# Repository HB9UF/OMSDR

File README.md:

# OMSDR: An SMD soldering practice kit for hams

## Introduction

OMSDR is a simple HF SDR receiver frontend inspired by the [SoftRock Lite II](http://fivedash.com/index.php?main_page=product_info&products_id=5). It is designed as SMD soldering practice kit to demonstrate the power of SMD technology, meant as an entry point for amateur radio hobbyists who are afraid of SMD. To allow for an easy entrance, most components are fairly large -- much larger than what you usually use in SMD designs. Our position is that SMD soldering is not hard if you know the proper techniques, and that a kit such as this one makes it easy to acquire these techniques. Note that this is not a particular good radio, and if you are not in for the aforementioned SMD aspects, you are probably better off with a different kit. If one of the following is of interest to you, though, then this may be for you:

1. Easy to assemble SMD kit with large parts and large footprints designed for entry level SMD hand soldering.
2. This kit makes for a good learning experience if you are interested in the Tayloe mixer circuitry that is the basis for these types of SDR frontends. The relevant signals are easy to probe, allowing for a deeper understanding of the circuit.

The circuit stored in this repository is designed for the 40 meter amateur radio band, although it is relatively easy (and hopefully instructional) to alter the design for operation on another band. If you do so, we would very much like to hear from you.

## Schematic

## Key differences to Soft Rock Lite II
This is not an exact copy of the design by Tony Parks. Instead, we opted for the following key differences:

- You don't have to wind any magnetic components. We use SMD inductors in the frontend filter (which we redesigned somewhat) and we use an SMD transformer (CX2147NL) for the balun.

- The original design employs a common-collector Colpitts oscillator to generate the reference for the local oscillator. We replaced that with a Silabs si5351 clock generator for versatility.

- The reference from the aforementioned Colpitts oscillation is fed into a dual D-Flip-Flop to generate a quadrature clock in the original design, yielding two square waves at a quarter of the reference frequency with a phase difference of 90°. We generate the quadrature clock directly with the si5351 clock generator.

- We use a microcontroller to program the clock generator. We chose an Attiny24 for this but this can be easily swapped out for something else. The clock generator is programmed via I2C and this bus is accessible through a pin header. Thus you could choose not to populate the microcontroller and use, e.g., a Raspberry Pi instead. Using a programmable clock generator allows us to change the center frequency of the SDR within the band, thus covering the whole 40 meter band. The original design has a fixed oscillator at approx. 7.056 MHz, thus even if you use a sampling rate of 96 kHz, it only covers the lower half of the band.

- a 3.5 mm audio jack can be plugged directly into the OMSDR board to connect to the sound card.

- Our design is fully open source.

## Bill of Materials

A BOM csv file is available [here](https://raw.githubusercontent.com/HB9UF/OMSDR/master/doc/BOM_rev1.2.csv) -- note that there is an aggregated table at the bottom. The `BOM` column follows the `bomtool` format, which is a retired tool by Alexis Lockwood. Essentially, digikey order numbers are prefixed with `DIST DIGIKEY` and for passives, we specify parts requirements that used to be processed by `bomtool` to pick the cheapest available part from digikey. Let us know if you are looking for a BOM or have compiled one yourself -- we have to transition to a new BOM format and that would be a good motivation to do so. Please also note that we did not include the pin headers because we believe that most builders will have those in bulk, and also because it pays off to buy them in bulk. For assembly, we have an interactive BOM [here](https://htmlpreview.github.io/?https://github.com/HB9UF/OMSDR/master/doc/ibom_rev1.2.html).

## Firmware

Firmware is available in the `firmware` subdirectory. To compile, run `make` and then flash the microcontroller using your favorite method, for example:

```
avrdude -v -pt44 -cstk500v2 -Pusb -Uflash:w:40m.hex:i
```

On a Debian system or a distribution based on Debian, you will need the packages `make`, `gcc-avr`, `avr-libc`, `binutils-avr` and `avrdude`  for this to work.

On power-up, the firmware cycles through the LEDs and initialized the local oscillator at 7.020 MHz. With a sound card sampling at 48 kHz, you will have access to the spectrum between 6.996 MHz and 7.044 MHz, i.e., the low end of the 40 meter amateur radio band. In this mode, the leftmost LED will be on and the remaining LEDs will be off: `[x][ ][ ][ ]`. Pushing the bottom button moves the center frequency to 7.060 MHz, covering the spectrum from 7.036 MHz to 7.084 MHz. The corresponding LED indicator reads `[x][x][ ][ ]`. In this manner, you can tune through different portions of the band according to the following frequency plan (center frequency indicated in parentheses):

```
       [x][ ][ ][ ]       [x][x][ ][ ]        [ ][x][x][ ]        [ ][ ][x][x]       [ ][ ][ ][x]
6.996  --(7.020)--  7.044
7.000  --(7.020)--  7.040
                    7.036  --(7.060)--  7.084
                    7.040  --(7.060)--  7.080
                                        7.076  --(7.100)--  7.124
                                        7.080  --(7.100)--  7.120
                                                            7.116  --(7.140)-- 7.164
                                                            7.120  --(7.140)-- 7.160
                                                                               7.156  --(7.180)-- 7.204
                                                                               7.160  --(7.180)-- 7.200
```

## Dimensions

## Software and License
This board files were designed with KiCad 6. They are licensed under the CC-BY-SA license. More information on this license can be found [here](https://creativecommons.org/licenses/by-sa/4.0/). The software is licensed under the [GNU GENERAL PUBLIC LICENSE Version 3](https://www.gnu.org/licenses/gpl-3.0.en.html)

## References

The paper "Ultra Low Noise, High Performance, Zero IF Quadrature Product Detector and Preamplifier" by Dan Tayloe is a nice introduction to the principles of Tayloe quadrature product detectors. We are not sure where it was published originally, but it is available [here](http://www.norcalqrp.org/files/Tayloe_mixer_x3a.pdf). For a more intricate introduction, including software aspects, we refer to the article series "A Software-Defined Radio for the Masses" by Gerald Youngblood, published in the QEX journal in 2002 and 2003: [Part 1](https://www.arrl.org/files/file/Technology/tis/info/pdf/020708qex013.pdf), [Part 2](https://www.arrl.org/files/file/Technology/tis/info/pdf/020910qex010.pdf), [Part 3](https://www.arrl.org/files/file/Technology/tis/info/pdf/021112qex027.pdf), [Part 4](https://www.arrl.org/files/file/Technology/tis/info/pdf/030304qex020.pdf).

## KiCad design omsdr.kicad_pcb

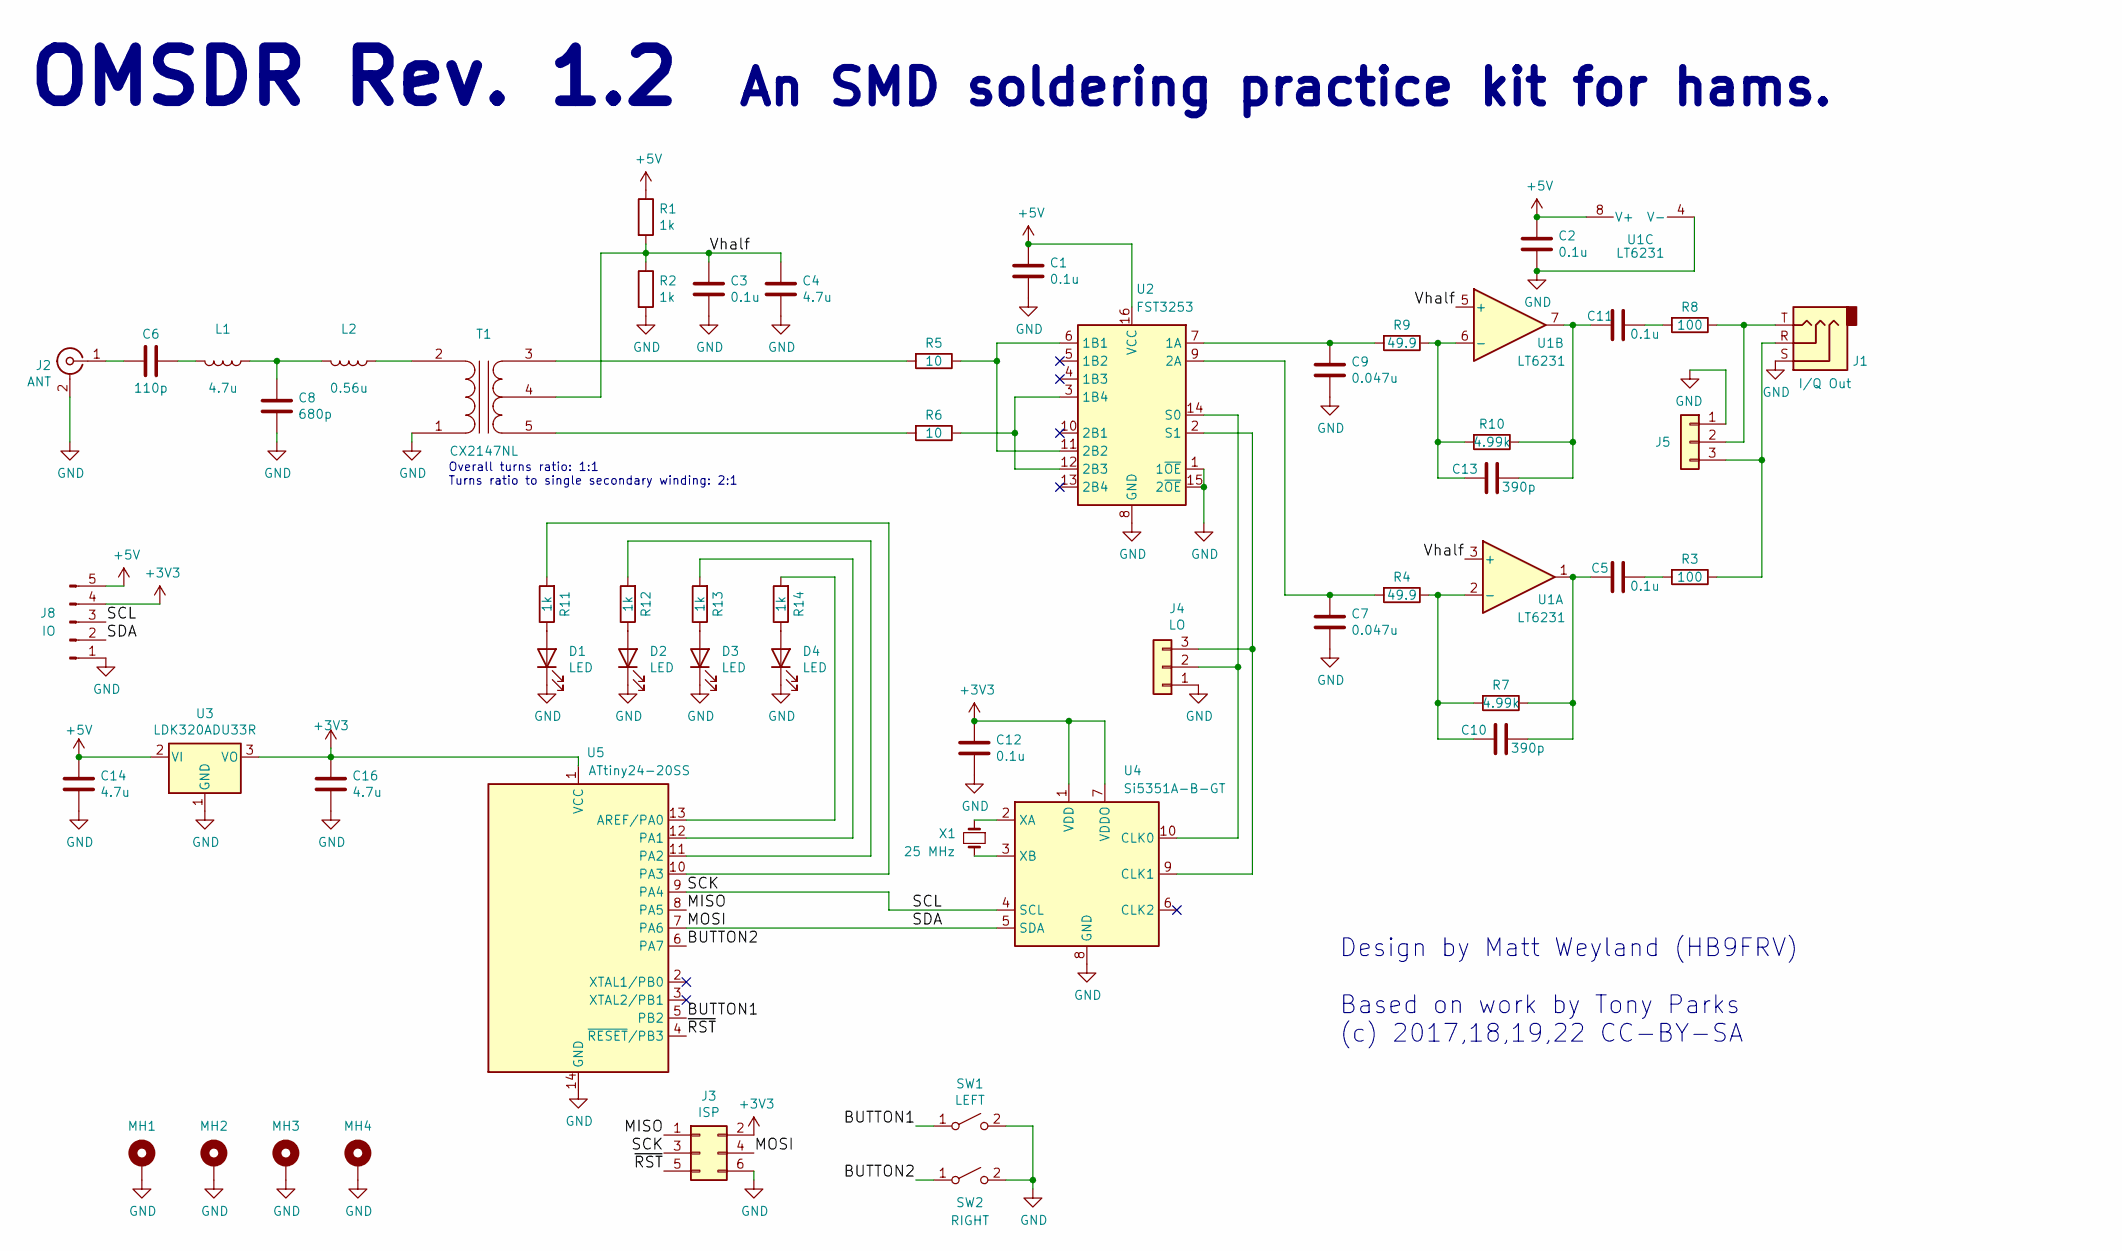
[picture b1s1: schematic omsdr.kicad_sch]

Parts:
C1, C2, C3, C5, C11, C12: 0.1u; C_1206_3216Metric_Pad1.33x1.80mm_HandSolder
C4, C14, C16: 4.7u; C_1206_3216Metric_Pad1.33x1.80mm_HandSolder
C6: 110p; C_1206_3216Metric_Pad1.33x1.80mm_HandSolder
C7, C9: 0.047u; C_1206_3216Metric_Pad1.33x1.80mm_HandSolder
C8: 680p; C_1206_3216Metric_Pad1.33x1.80mm_HandSolder
C10, C13: 390p; C_1206_3216Metric_Pad1.33x1.80mm_HandSolder
D1, D2, D3, D4: LED; LED_0805_2012Metric_Pad1.15x1.40mm_HandSolder
J1: I/Q Out; Jack_3.5mm_CUI_SJ-3523-SMT_Horizontal
J2: ANT; SMA_Samtec_SMA-J-P-X-ST-EM1_EdgeMount
J3: ISP; PinHeader_2x03_P2.54mm_Vertical
J4: LO; PinHeader_1x03_P2.54mm_Vertical
J5: I/Q Out; PinHeader_1x03_P2.54mm_Vertical
J8: IO; PinHeader_1x05_P2.54mm_Horizontal
L1: 4.7u; L_1206_3216Metric_Pad1.42x1.75mm_HandSolder
L2: 0.56u; L_0805_2012Metric_Pad1.15x1.40mm_HandSolder
MH1, MH2, MH3, MH4: MountingHole_3.2mm_M3_Pad_Via
R1, R2, R11, R12, R13, R14: 1k; R_1206_3216Metric_Pad1.30x1.75mm_HandSolder
R3, R8: 100; R_1206_3216Metric_Pad1.30x1.75mm_HandSolder
R4, R9: 49.9; R_1206_3216Metric_Pad1.30x1.75mm_HandSolder
R5, R6: 10; R_1206_3216Metric_Pad1.30x1.75mm_HandSolder
R7, R10: 4.99k; R_1206_3216Metric_Pad1.30x1.75mm_HandSolder
SW1: LEFT; SW_SPST_TL3342
SW2: RIGHT; SW_SPST_TL3342
T1: CX2147NL; CX2074
U1: LT6231; SO-8_3.9x4.9mm_P1.27mm
U2: FST3253; SOIC-16_3.9x9.9mm_P1.27mm
U3: LDK320ADU33R; SOT-89-3_Handsoldering
U4: Si5351A-B-GT; MSOP-10_3x3mm_P0.5mm
U5: ATtiny24-20SS; SOIC-14_3.9x8.7mm_P1.27mm
X1: 25 MHz; Crystal_SMD_HC49-SD

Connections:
+3V3: C12.1, C16.1, J3.2, J8.4, U3.3 (VO), U4.1 (VDD), U4.7 (VDDO), U5.1 (VCC)
+5V: C1.1, C2.1, C14.1, J8.5, R1.1, U1.8 (V+), U2.16 (VCC), U3.2 (VI)
/BUTTON1: SW1.1 (A), U5.5 (PB2)
/BUTTON2: SW2.1 (A), U5.6 (PA7)
/MISO: J3.1, U5.8 (PA5)
/MOSI: J3.4, J8.2, U4.5 (SDA), U5.7 (PA6)
/SCK: J3.3, J8.3, U4.4 (SCL), U5.9 (PA4)
/Vhalf: C3.1, C4.1, R1.2, R2.1, T1.4 (SC), U1.3 (+), U1.5 (+)
/~RST: J3.5, U5.4 (~RESET/PB3)
GND: C1.2, C2.2, C3.2, C4.2, C7.2, C8.2, C9.2, C12.2, C14.2, C16.2, D1.1 (K), D2.1 (K), D3.1 (K), D4.1 (K), J1.S, J2.2 (Ext), J3.6, J4.1, J5.1, J8.1, MH1.1, MH2.1, MH3.1, MH4.1, R2.2, SW1.2 (B), SW2.2 (B), T1.1 (AA), U1.4 (V-), U2.1 (1~OE), U2.8 (GND), U2.15 (2~OE), U3.1 (GND), U4.8 (GND), U5.14 (GND)
unnamed: C5.2, R3.2
unnamed: C6.1, L1.2
unnamed: C6.2, J2.1 (In)
unnamed: C7.1, R4.2, U2.9 (2A)
unnamed: C8.1, L1.1, L2.2
unnamed: C9.1, R9.2, U2.7 (1A)
unnamed: C10.1, R4.1, R7.2, U1.2 (-)
unnamed: C5.1, C10.2, R7.1, U1.1
unnamed: C11.1, C13.2, R10.1, U1.7
unnamed: C11.2, R8.2
unnamed: C13.1, R9.1, R10.2, U1.6 (-)
unnamed: D1.2 (A), R11.1
unnamed: D2.2 (A), R12.1
unnamed: D3.2 (A), R13.1
unnamed: D4.2 (A), R14.1
unnamed: J1.R, J5.3, R3.1
unnamed: J1.T, J5.2, R8.1
unnamed: J4.2, U2.14 (S0), U4.10 (CLK0)
unnamed: J4.3, U2.2 (S1), U4.9 (CLK1)
unnamed: L2.1, T1.2 (AB)
unnamed: R5.1, U2.6 (1B1), U2.11 (2B2)
unnamed: R5.2, T1.3 (SA)
unnamed: R6.1, U2.3 (1B4), U2.12 (2B3)
unnamed: R6.2, T1.5 (SB)
unnamed: R11.2, U5.10 (PA3)
unnamed: R12.2, U5.11 (PA2)
unnamed: R13.2, U5.12 (PA1)
unnamed: R14.2, U5.13 (AREF/PA0)
unnamed: U4.2 (XA), X1.1
unnamed: U4.3 (XB), X1.2

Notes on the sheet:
An SMD soldering practice kit for hams.
Overall turns ratio: 1:1 Turns ratio to single secondary winding: 2:1
Design by Matt Weyland (HB9FRV) Based on work by Tony Parks (c) 2017,18,19,22 CC-BY-SA
OMSDR Rev. 1.2

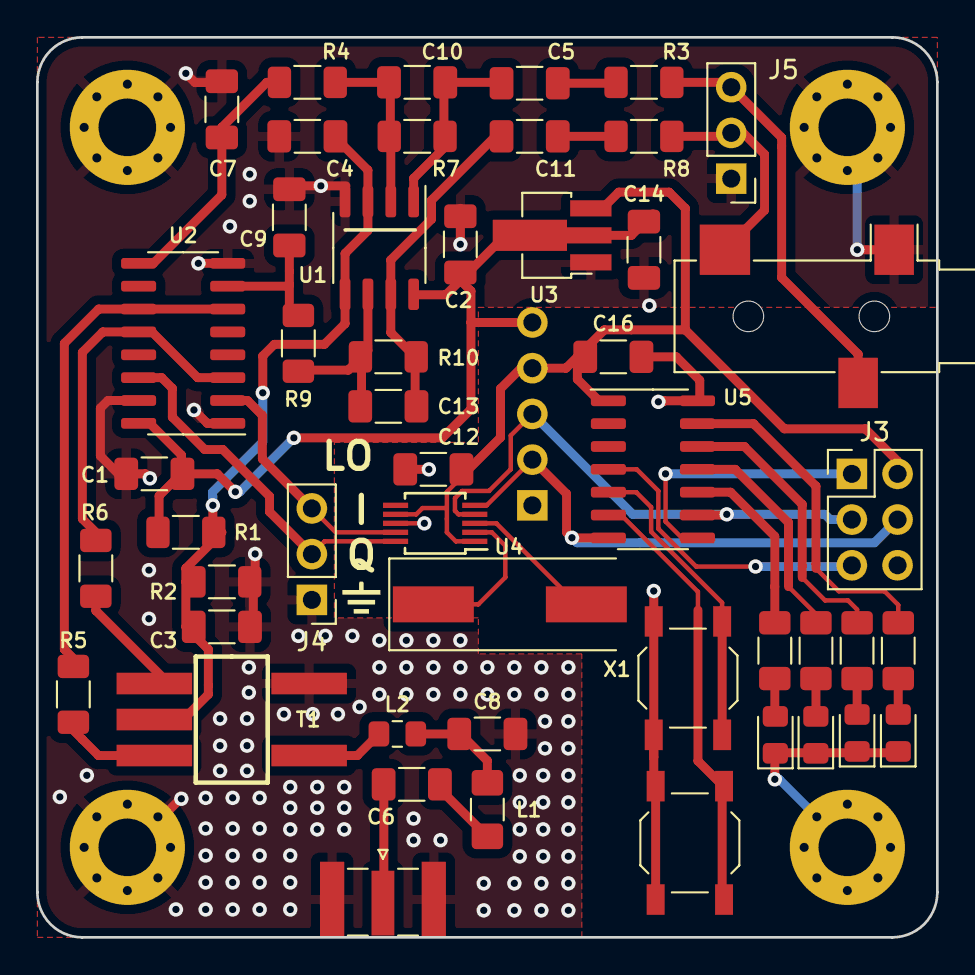
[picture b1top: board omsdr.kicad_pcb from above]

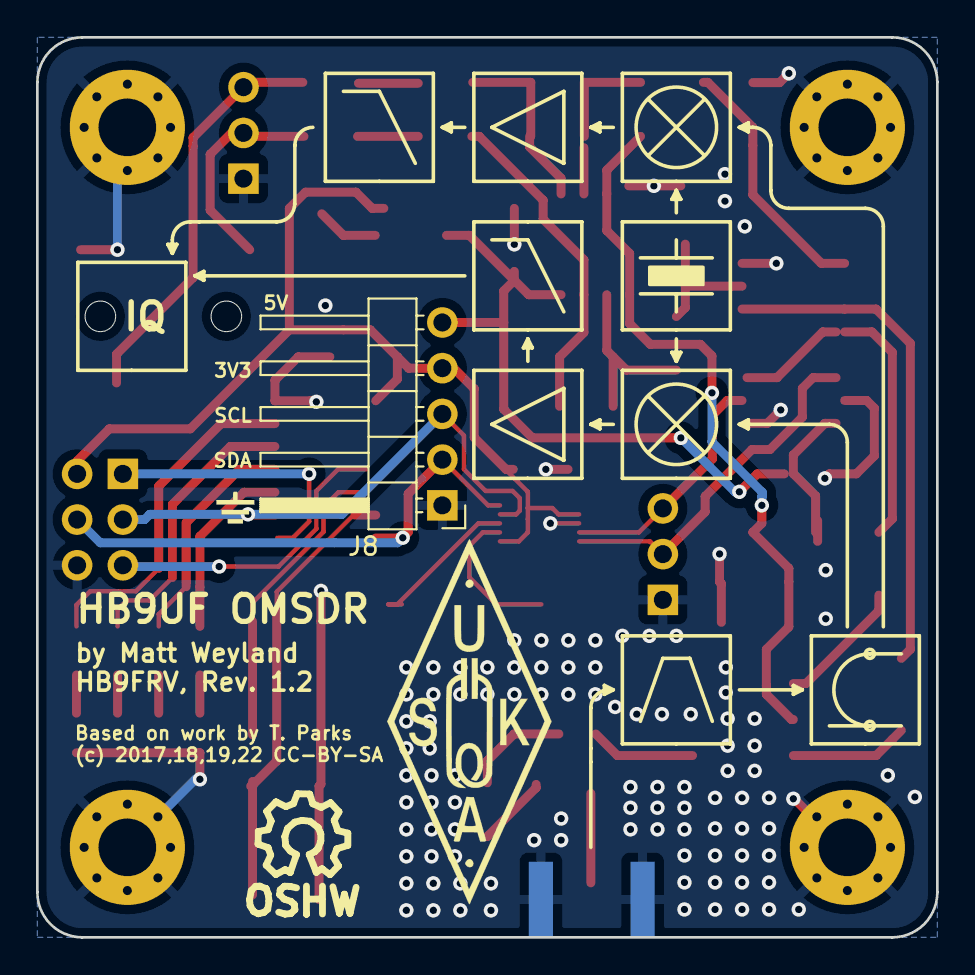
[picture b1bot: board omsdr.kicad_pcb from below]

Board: 2 copper layers, 50.0 x 50.0 mm, 57 parts (3 on the bottom side), 40 nets.

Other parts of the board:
SYM: Symbol_OSHW-Logo_SilkScreen_07Jul2012; Symbol_OSHW-Logo_SilkScreen
VAL: GND
VAL#2: GND

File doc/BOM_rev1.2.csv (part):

"Individual Components:"

"Item","Qty","Reference(s)","Value","LibPart","Footprint","Datasheet","BOM"
"","","C1","0.1u","Device:C","Capacitor_SMD:C_1206_3216Metric_Pad1.33x1.80mm_HandSolder","~","CAP MLCC 0.1u  ±10% ≥X7R [1206]"
"","","C2","0.1u","Device:C","Capacitor_SMD:C_1206_3216Metric_Pad1.33x1.80mm_HandSolder","~","CAP MLCC 0.1u  ±10% ≥X7R [1206]"
"","","C3","0.1u","Device:C","Capacitor_SMD:C_1206_3216Metric_Pad1.33x1.80mm_HandSolder","~","CAP MLCC 0.1u  ±10% ≥X7R [1206]"
"","","C4","4.7u","Device:C","Capacitor_SMD:C_1206_3216Metric_Pad1.33x1.80mm_HandSolder","~","CAP MLCC 4.7u ±20% 10V [1206]"
"","","C5","0.1u","Device:C","Capacitor_SMD:C_1206_3216Metric_Pad1.33x1.80mm_HandSolder","~","CAP MLCC 0.1u  ±10% ≥X7R [1206]"
"","","C6","110p","Device:C","Capacitor_SMD:C_1206_3216Metric_Pad1.33x1.80mm_HandSolder","~","CAP MLCC 110p ±5% NP0 [1206]"
"","","C7","0.047u","Device:C","Capacitor_SMD:C_1206_3216Metric_Pad1.33x1.80mm_HandSolder","~","CAP MLCC 0.047u ±10% ≥X5R [1206]"
"","","C8","680p","Device:C","Capacitor_SMD:C_1206_3216Metric_Pad1.33x1.80mm_HandSolder","~","CAP MLCC 680p  ±5% NP0 [1206]"
"","","C9","0.047u","Device:C","Capacitor_SMD:C_1206_3216Metric_Pad1.33x1.80mm_HandSolder","~","CAP MLCC 0.047u ±10% ≥X5R [1206]"
"","","C10","390p","Device:C","Capacitor_SMD:C_1206_3216Metric_Pad1.33x1.80mm_HandSolder","~","CAP MLCC 390p  ±5% NP0 [1206]"
"","","C11","0.1u","Device:C","Capacitor_SMD:C_1206_3216Metric_Pad1.33x1.80mm_HandSolder","~","CAP MLCC 0.1u  ±10% ≥X7R [1206]"
"","","C12","0.1u","Device:C","Capacitor_SMD:C_1206_3216Metric_Pad1.33x1.80mm_HandSolder","~","CAP MLCC 0.1u  ±10% ≥X7R [1206]"
"","","C13","390p","Device:C","Capacitor_SMD:C_1206_3216Metric_Pad1.33x1.80mm_HandSolder","~","CAP MLCC 390p  ±5% NP0 [1206]"
"","","C14","4.7u","Device:C","Capacitor_SMD:C_1206_3216Metric_Pad1.33x1.80mm_HandSolder","~","CAP MLCC 4.7u ±20% 10V [1206]"
"","","C16","4.7u","Device:C","Capacitor_SMD:C_1206_3216Metric_Pad1.33x1.80mm_HandSolder","~","CAP MLCC 4.7u ±20% 10V [1206]"
"","","D1","LED","Device:LED","LED_SMD:LED_0805_2012Metric_Pad1.15x1.40mm_HandSolder","~","DIST DIGIKEY 732-4984-1-ND"
"","","D2","LED","Device:LED","LED_SMD:LED_0805_2012Metric_Pad1.15x1.40mm_HandSolder","~","DIST DIGIKEY 732-4984-1-ND"
"","","D3","LED","Device:LED","LED_SMD:LED_0805_2012Metric_Pad1.15x1.40mm_HandSolder","~","DIST DIGIKEY 732-4984-1-ND"
"","","D4","LED","Device:LED","LED_SMD:LED_0805_2012Metric_Pad1.15x1.40mm_HandSolder","~","DIST DIGIKEY 732-4984-1-ND"
"","","J1","I/Q Out","Connector:AudioJack3","Connector_Audio:Jack_3.5mm_CUI_SJ-3523-SMT_Horizontal","~","DIST DIGIKEY CP-3523SJCT-ND"
"","","J2","ANT","Connector:Conn_Coaxial","Connector_Coaxial:SMA_Samtec_SMA-J-P-X-ST-EM1_EdgeMount"," ~","DIST DIGIKEY CON-SMA-EDGE-S-ND "
"","","J3","ISP","Connector_Generic:Conn_02x03_Odd_Even","Connector_PinHeader_2.54mm:PinHeader_2x03_P2.54mm_Vertical","~","DIST DIGIKEY 609-2846-ND"
"","","J4","LO","Connector_Generic:Conn_01x03","Connector_PinHeader_2.54mm:PinHeader_1x03_P2.54mm_Vertical","~",""
"","","J5","I/Q Out","Connector_Generic:Conn_01x03","Connector_PinHeader_2.54mm:PinHeader_1x03_P2.54mm_Vertical","~",""
"","","J8","IO","Connector:Conn_01x05_Male","Connector_PinHeader_2.54mm:PinHeader_1x05_P2.54mm_Horizontal","~",""
"","","L1","4.7u","Device:L","Inductor_SMD:L_1206_3216Metric_Pad1.42x1.75mm_HandSolder","~","DIST DIGIKEY  587-2034-1-ND"
"","","L2","0.56u","Device:L","Inductor_SMD:L_0805_2012Metric_Pad1.15x1.40mm_HandSolder","~","DIST DIGIKEY  LBM2016TR56J"
"","","MH1","","Mechanical:MountingHole_Pad","MountingHole:MountingHole_3.2mm_M3_Pad_Via","~",""
"","","MH2","","Mechanical:MountingHole_Pad","MountingHole:MountingHole_3.2mm_M3_Pad_Via","~",""
"","","MH3","","Mechanical:MountingHole_Pad","MountingHole:MountingHole_3.2mm_M3_Pad_Via","~",""
"","","MH4","","Mechanical:MountingHole_Pad","MountingHole:MountingHole_3.2mm_M3_Pad_Via","~",""
"","","R1","1k","Device:R","Resistor_SMD:R_1206_3216Metric_Pad1.30x1.75mm_HandSolder","~","RES SMD 1k 1% [1206]"
"","","R2","1k","Device:R","Resistor_SMD:R_1206_3216Metric_Pad1.30x1.75mm_HandSolder","~","RES SMD 1k 1% [1206]"
"","","R3","100","Device:R","Resistor_SMD:R_1206_3216Metric_Pad1.30x1.75mm_HandSolder","~","RES SMD 100 1% [1206]"
"","","R4","49.9","Device:R","Resistor_SMD:R_1206_3216Metric_Pad1.30x1.75mm_HandSolder","~","RES SMD 49.9 1% [1206]"
"","","R5","10","Device:R","Resistor_SMD:R_1206_3216Metric_Pad1.30x1.75mm_HandSolder","~","RES SMD 10 1% [1206]"
"","","R6","10","Device:R","Resistor_SMD:R_1206_3216Metric_Pad1.30x1.75mm_HandSolder","~","RES SMD 10 1% [1206]"
"","","R7","4.99k","Device:R","Resistor_SMD:R_1206_3216Metric_Pad1.30x1.75mm_HandSolder","~","RES SMD 4.99k 1% [1206]"
"","","R8","100","Device:R","Resistor_SMD:R_1206_3216Metric_Pad1.30x1.75mm_HandSolder","~","RES SMD 100 1% [1206]"
"","","R9","49.9","Device:R","Resistor_SMD:R_1206_3216Metric_Pad1.30x1.75mm_HandSolder","~","RES SMD 49.9 1% [1206]"
"","","R10","4.99k","Device:R","Resistor_SMD:R_1206_3216Metric_Pad1.30x1.75mm_HandSolder","~","RES SMD 4.99k 1% [1206]"
"","","R11","1k","Device:R","Resistor_SMD:R_1206_3216Metric_Pad1.30x1.75mm_HandSolder","~","RES SMD 1k 1% [0805]"
"","","R12","1k","Device:R","Resistor_SMD:R_1206_3216Metric_Pad1.30x1.75mm_HandSolder","~","RES SMD 1k 1% [0805]"
"","","R13","1k","Device:R","Resistor_SMD:R_1206_3216Metric_Pad1.30x1.75mm_HandSolder","~","RES SMD 1k 1% [0805]"
"","","R14","1k","Device:R","Resistor_SMD:R_1206_3216Metric_Pad1.30x1.75mm_HandSolder","~","RES SMD 1k 1% [0805]"
"","","SW1","LEFT","Switch:SW_SPST","Button_Switch_SMD:SW_SPST_TL3342","~","DIST DIGIKEY EG2531CT-ND"
"","","SW2","RIGHT","Switch:SW_SPST","Button_Switch_SMD:SW_SPST_TL3342","~","DIST DIGIKEY EG2531CT-ND"
"","","T1","CX2147NL","Device:Transformer_1P_SS","local:CX2074","~","DIST DIGIKEY 553-1501-ND"
"","","U1","LT6231","Amplifier_Operational:LT6234","Package_SO:SO-8_3.9x4.9mm_P1.27mm","https://www.analog.com/media/en/technical-documentation/data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","DIST DIGIKEY  LT6231CS8#PBF-ND"
"","","U2","FST3253","Analog_Switch:SN74CBT3253","Package_SO:SOIC-16_3.9x9.9mm_P1.27mm","https://www.fairchildsemi.com/datasheets/FS/FST3253.pdf","DIST DIGIKEY 296-19206-1-ND"
"","","U3","LDK320ADU33R","Regulator_Linear:MCP1703A-3302_SOT89","Package_TO_SOT_SMD:SOT-89-3_Handsoldering","http://ww1.microchip.com/downloads/en/DeviceDoc/20005122B.pdf","DIST DIGIKEY 497-17585-1-ND"
"","","U4","Si5351A-B-GT","Oscillator:Si5351A-B-GT","Package_SO:MSOP-10_3x3mm_P0.5mm","https://www.silabs.com/documents/public/data-sheets/Si5351-B.pdf","DIST DIGIKEY 336-3908-1-ND"
"","","U5","ATtiny24-20SS","MCU_Microchip_ATtiny:ATtiny24-20SS","Package_SO:SOIC-14_3.9x8.7mm_P1.27mm","http://ww1.microchip.com/downloads/en/DeviceDoc/doc8006.pdf","DIST DIGIKEY  ATTINY24A-SSU-ND"
"","","X1","25 MHz","Device:Crystal_Small","Crystal:Crystal_SMD_HC49-SD","~","DIST DIGIKEY  535-10235-1-ND"



"Collated Components:"

"Item","Qty","Reference(s)","Value","LibPart","Footprint","Datasheet","BOM"
"1","6","C1, C2, C3, C5, C11, C12","0.1u","Device:C","Capacitor_SMD:C_1206_3216Metric_Pad1.33x1.80mm_HandSolder","~","CAP MLCC 0.1u  ±10% ≥X7R [1206]"
"2","3","C4, C14, C16","4.7u","Device:C","Capacitor_SMD:C_1206_3216Metric_Pad1.33x1.80mm_HandSolder","~","CAP MLCC 4.7u ±20% 10V [1206]"
"3","1","C6","110p","Device:C","Capacitor_SMD:C_1206_3216Metric_Pad1.33x1.80mm_HandSolder","~","CAP MLCC 110p ±5% NP0 [1206]"
"4","2","C7, C9","0.047u","Device:C","Capacitor_SMD:C_1206_3216Metric_Pad1.33x1.80mm_HandSolder","~","CAP MLCC 0.047u ±10% ≥X5R [1206]"
"5","1","C8","680p","Device:C","Capacitor_SMD:C_1206_3216Metric_Pad1.33x1.80mm_HandSolder","~","CAP MLCC 680p  ±5% NP0 [1206]"
"6","2","C10, C13","390p","Device:C","Capacitor_SMD:C_1206_3216Metric_Pad1.33x1.80mm_HandSolder","~","CAP MLCC 390p  ±5% NP0 [1206]"
"7","4","D1, D2, D3, D4","LED","Device:LED","LED_SMD:LED_0805_2012Metric_Pad1.15x1.40mm_HandSolder","~","DIST DIGIKEY 732-4984-1-ND"
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
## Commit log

2018-01-10 Initial commit on the road to v1.1
2018-01-10 Initial commit of local 3d models
2018-01-10 Fix paths to local 3d models
2018-01-10 Adding utility to generate 2d renders using gerbv
2018-01-17 Replace 3.3 V regul L78L33ABUTR with LDK320ADU33R
    Almost same price, lower noise, better PSSR and slightly better
    pinout. Same SOT-89 package. Chances in schematic and PCB.
2018-01-18 Replacing crystal 3d model with step file that renders properly.
2018-01-21 Added missing silk screen line
2018-01-21 Don't create gerber report
2018-02-06 register_map_5mc_10mc.txt file for 5 MHz / 10 MHz test pattern with bus pirate
2018-02-06 Adding LICENSE file for code that will follow.
2018-02-06 Adding simple blink program to test microcontroller
2018-02-06 Moving blink.c and Makefile out of subdirectory
2018-02-13 Changed sample cap loading resistor frorm 10 Ohms to 49.9 Ohms
2018-02-13 Component values for opamp feedback network
2018-02-13 Multiplexer chip EOL, replaced with substitute order number
2019-03-14 Updating PCB from schematic (no formal changes)
2019-03-15 Adding more component values and BOM digikey order numbers
2019-03-15 Changes due to new kicad version (library upgrades etc.)
2019-03-15 Change Makefile.blink from attiny44 to attiny24
2019-03-15 Bumping kicad-schlib to latest version of upstream
2019-03-15 Use FST3253 from kicad-schlib instead of cached
2019-03-17 Replacing SMA connector since the one used was phased out from kicad
    No BOM as we are better off ordering this from China
2019-03-17 Changed my mind: Swapped SMA edge connector for smaller version
2019-03-17 Fixed silk screen of filter icon on back side of PCB
2019-03-17 Adding line to silk screen to indicate tiled edge of LT6231 package
2019-03-17 Reworked input bandpass filter
2019-03-17 Updated copyright dates
2019-03-17 Replaced footprints with versions from new kicad footprint library
2019-03-17 Adding pin header for IQ audio tap
2019-03-17 Replaced connector footprints with versions from new kicad footprint library
2019-03-17 Adding missing BOM fields
2019-03-17 Bumping version to 1.2 on schematic and PCB
2019-05-20 New copyright owners for 1.2 version of the project.
2019-05-20 Now official HB9UF project, add logo and rework silk.
2022-01-25 Bumping to KiCad version 6.0
2022-01-25 Adding year 2022 to copyright info
2022-01-25 Using attiny24 from the KiCad library (sch & pcb)
2022-01-25 Using LC6231 from the KiCad library (sch & pcb)
2022-01-25 Using headphone connector from the KiCad library (sch & pcb)
2022-01-25 Using Si5351 from the KiCad library (sch & pcb)
2022-01-25 Using FST3253 from the KiCad library (sch & pcb)
2022-01-25 Replacing some passives with current kicad symbols/footprints
2022-01-25 Removing old libraries and unneeded footprints
2022-01-25 Using M3 mouting holes from the KiCad library (sch & pcb)
2022-01-25 Removing kicad-pcblib submodule (dependency was removed)
2022-01-25 Registering 3D model of headphone jack
2022-01-25 Cleanup to satisfy DRC
2022-01-25 Removing stale 3D model for SMA connector
2022-01-25 Fixing BOM entry for SMA connector
2022-01-25 Removing rescue and cache files since symbols are embedded in KiCad 6
2022-01-25 Setting solder mask clearance to 0
    Board house will use their own value and modify the gerbers.
2022-01-26 Using crystal footprint from the KiCad library (pcb & 3d model)
2022-01-26 Replacing push buttons with current kicad footprints and 3d models
2022-01-27 Initial commit of firmware
2022-01-27 Reducing size of affiliation text on schematic
2022-01-27 Adding schematics of rev 1.2 board (pdf and png)
2022-01-27 Removing csv files from .gitignore (useful for BOM)
2022-01-27 Adding BOM csv for rev 1.2
2022-01-27 Adding interactive BOM for rev 1.2.
2022-01-27 Updating copyright in LICENSE file
2022-01-27 Initial commit of README.md file
2022-01-27 Removing old tests/ subdirectory and submodule
2022-01-29 Replacing wrong balun with correct part
    We used some 1:4 part, but we really should use a 1:1 part with
    center tap. Otherwise the impedance seen when looking into the
    atenna port will be way off. What we really need to see is the
    sampling cap (a short to GND at RF frequencies), followed by the
    internal switch resistance (5 ish Ohm or so?), followed by the
    10 Ohm series resistor, i.e. a total of 15ish Ohm multiplied by
2022-01-29 Updating 2d render script to new kicad nomenclature
2022-01-29 Preparing for gerber file generation
    - Reduce size of stencil holes by 15%
    - Position board thickness comment appropriately
    - Position dimensional arrows appropriately
2022-01-29 Adding 2d render with diemnsions to README
